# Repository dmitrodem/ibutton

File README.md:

# ibutton
iButton emulator on attiny13

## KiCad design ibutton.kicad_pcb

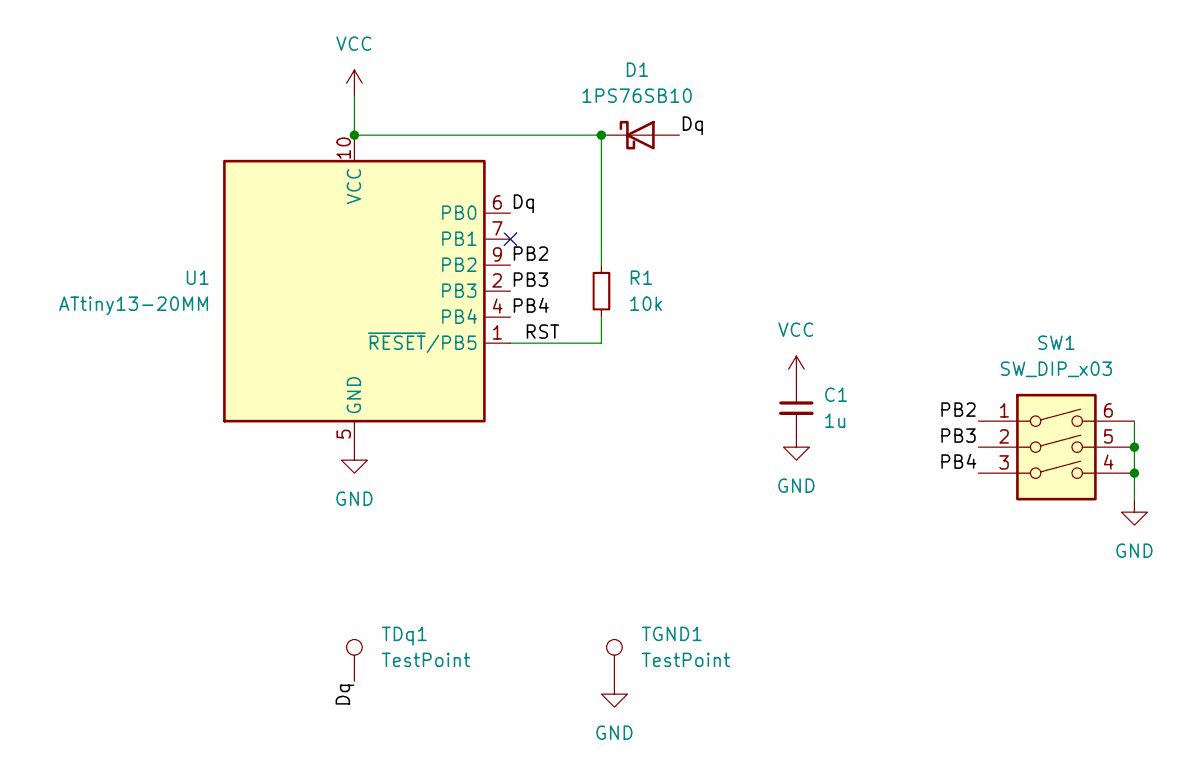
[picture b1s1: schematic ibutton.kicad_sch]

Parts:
C1: 1u; C_0603_1608Metric
D1: 1PS76SB10; D_SOD-323
R1: 10k; R_0402_1005Metric
SW1: SW_DIP_x03; SW_DIP_SPSTx03_Slide_KingTek_DSHP03TS_W7.62mm_P1.27mm
TDq1: TestPoint; TestPoint_Pad_D1.0mm
TGND1: TestPoint; TestPoint_Pad_D1.0mm
U1: ATtiny13-20MM; DFN-10-1EP_3x3mm_P0.5mm_EP1.75x2.7mm

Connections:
/Dq: D1.2 (A), TDq1.1, U1.6 (PB0)
/PB2: SW1.1, U1.9 (PB2)
/PB3: SW1.2, U1.2 (PB3)
/PB4: SW1.3, U1.4 (PB4)
/RST: R1.2, U1.1 (~RESET/PB5)
GND: C1.2, SW1.4, SW1.5, SW1.6, TGND1.1, U1.5 (GND), U1.11 (GND)
VCC: C1.1, D1.1 (K), R1.1, U1.10 (VCC)

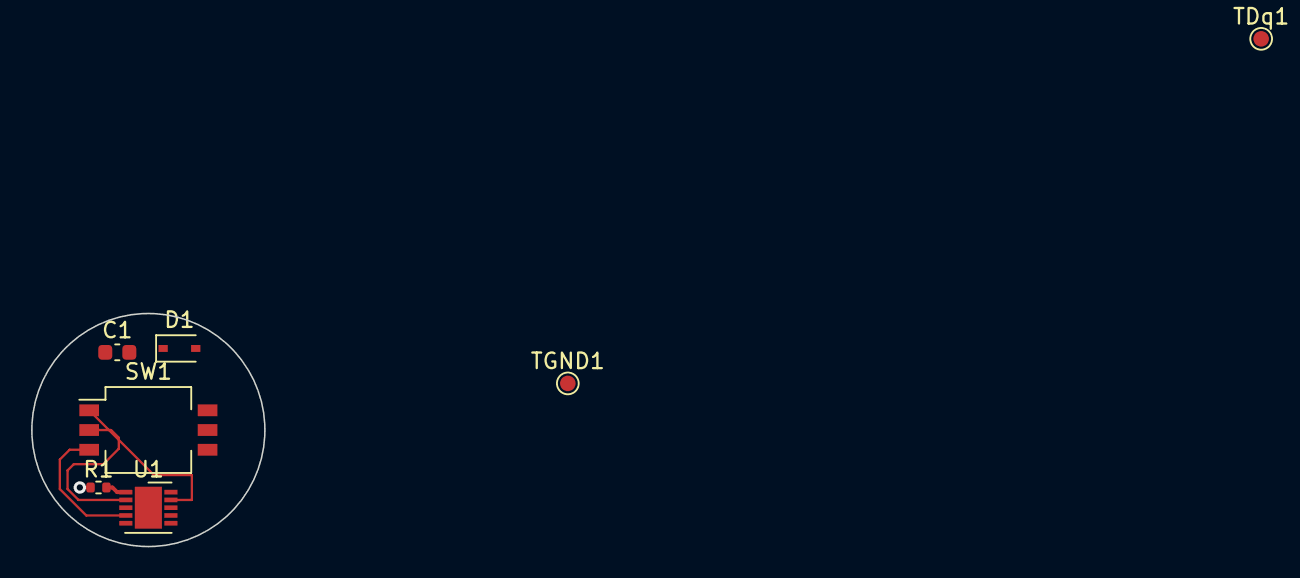
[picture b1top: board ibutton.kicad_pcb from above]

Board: 2 copper layers, 15.0 x 15.0 mm, 7 parts (0 on the bottom side), 7 nets.

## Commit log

2021-12-23 Sch & Pcb
